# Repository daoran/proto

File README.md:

# proto

`proto` contain notes and code used to learn about different aspects of
robotics. From estimation, mapping to control and planning.

## Build

For convenience there is a `Makefile` that automates the installation of
dependencies and building of `proto`, the make targets are as follows.

```
  deps:
    Install proto dependencies.

  debug:
    Build proto in debug mode.

  release:
    Build proto in release mode.

  install:
    Install proto to $PREFIX. By default this is "/usr/local".

  ros:
    Build the ROS interface to `proto` (a.k.a `proto_ros`).

  format_code:
    Format proto code using clang-format.
```

Or, the standard way to build a C++ project is to enter the following commands
at the root of the repo.

```
  mkdir -p build
  cd build
  cmake ..
  make
  sudo make install  # By default will install to /usr/local
```

## License

The source code is released under MIT license.

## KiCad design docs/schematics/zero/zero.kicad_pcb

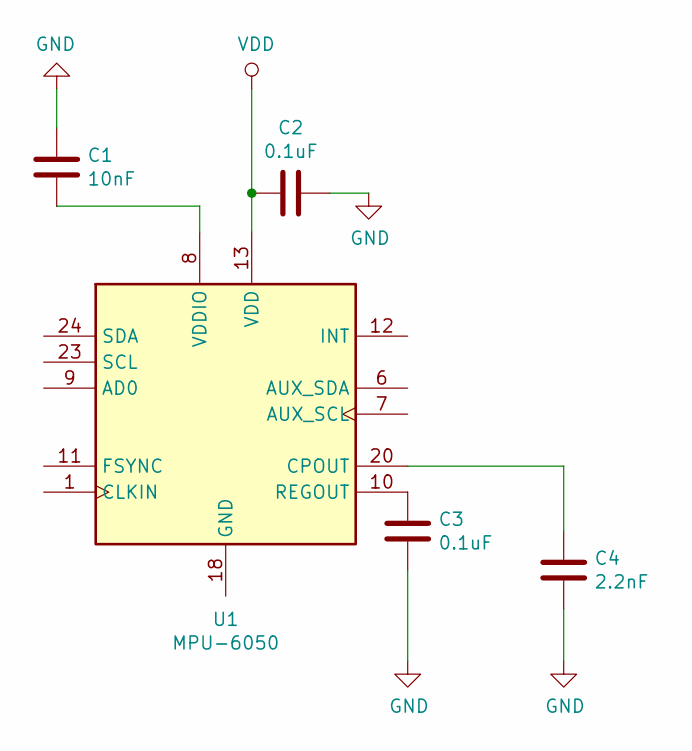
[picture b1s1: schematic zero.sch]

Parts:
C1: 10nF; C_0805_2012Metric
C2, C3: 0.1uF; C_0805_2012Metric
C4: 2.2nF; C_0805_2012Metric
U1: MPU-6050; InvenSense_QFN-24_4x4mm_P0.5mm

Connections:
GND: C1.1, C2.1, C3.2, C4.1
unnamed: C1.2, U1.8 (VDDIO)
unnamed: C3.1, U1.10 (REGOUT)
unnamed: C4.2, U1.20 (CPOUT)
VDD: C2.2, U1.13 (VDD)

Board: 2 copper layers, 5 parts (0 on the bottom side), 5 nets, no tracks yet.

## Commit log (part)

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2024-12-14 Add KDTree to xyz.py
2024-12-14 fix python paths
2024-12-15 Remove scripts/utils
2024-12-15 Remove realsense PwM trigger
2024-12-15 Remove fcu kicad files
2024-12-15 Remove old scripts
2024-12-15 Update exps readme
2024-12-15 Remove old doc
2024-12-15 fix tests and general clean up
2024-12-15 Add gl_entity utility functions
2024-12-15 Rename vector and matrix functions
2024-12-15 Add ability to draw 3D point clouds
2024-12-15 Add points frag and vertex shaders
2024-12-16 Add orbit controls
2024-12-17 Add gl rectangle
2024-12-17 Constrain pitch while rotating camera
2024-12-20 Remove tis and sbgc from xyz.h
2024-12-25 Add KHR and glad
2024-12-25 Modify Makefile for FreeType and GLAD
2024-12-25 Add glad to gitignore
2024-12-26 Add ability to render text
2024-12-26 Add gl_line functions
2024-12-29 Add working gl_image_t
2024-12-31 Update gui
2024-12-31 Move shaders inline
2024-12-31 Remove shaders dir
2024-12-31 Add working button
2025-01-01 Add ability to draw text background
2025-01-04 Complete revamp of notes
2025-01-04 Add fonts
2025-01-04 Fix text not blending background
2025-01-08 Fix text rendering
2025-01-12 Refactor
2025-01-12 Refactor gl_rect functions to use gl_shader_t
2025-01-12 Refactor gl_cube functions to use gl_shader_t
2025-01-12 Refactor draw functions
2025-01-12 Add text_width_height()
2025-01-14 Start working on ui_menu()
2025-01-14 Fix mouse
2025-01-15 Refactor gl_image_t to draw_image()
2025-01-16 Fix button
2025-01-17 Make gui variables global
2025-01-19 Add http.c
2025-01-20 Add gl_vec3_t gl_quat_t gl_pose_t
2025-01-20 Add ambient and spectral lighting to cube
2025-01-23 Add prefix xyz to sources
2025-01-24 Move mav out of src
2025-01-24 Extracting out functions into separate files
2025-01-25 Restructure build
2025-01-26 Restructure
2025-01-26 Fix tests
2025-01-26 Disable euroc test in CI mode
2025-01-26 Fix test
2025-02-03 Add cam_checkerboard to euroc dataset download script
2025-02-03 Add WIP checkerboard_detection.py
2025-02-08 Remove UI elements
2025-02-09 Add print_float_array() print_double_array()
2025-02-09 Add xyz_kitti module
2025-02-09 Add comments
2025-02-16 Add kitti_calib_print()
2025-02-23 Add FLANN as third party
2025-02-23 Add lz4 to third_party
2025-02-23 Update third_party/Makefile
2025-02-23 Add xyz_octree
2025-02-23 Remove pyqtgraph code
2025-02-23 Remove pip_install()
2025-02-23 Remove Gimbal Calibrator
2025-02-23 Fix ts2sec() type hints
2025-02-28 Add umeyama()
2025-02-28 Minor refactor
2025-02-28 Add KittiVelodyneData()
2025-02-28 Make xyz_aprilgrid self sufficient
2025-03-01 Mkae xyz_kitti self sufficient
2025-03-01 Make xyz_control self sufficient
2025-03-02 Add TestPointCloud
2025-03-02 Add .venv to .gitignore
2025-03-03 Add fix_rotation_matrix()
2025-03-03 Update euler321() type hinting
2025-03-03 Remove CameraFactor
2025-03-04 Add rot_diff()
2025-03-04 Add test_icp()
2025-03-08 Remove malloc and calloc macros for gui
2025-03-09 Refactor entities
2025-03-09 Minor updates
2025-03-16 Fix bug in KITTI oxts satellite data
2025-03-16 Refactor gl entities
2025-03-16 Update tests
2025-03-19 Add wait_key()
2025-03-19 Add dotf()
2025-03-19 Add VEC_ADD() and VEC_SUB()
2025-03-19 Add test_idf_factor()
2025-03-19 Remove prints in unittest
2025-03-19 Add point_t
2025-03-26 Add xyz_voxel module
2025-04-05 Refactor out MALLOC() and CALLOC() macros
2025-04-09 Add kdtree_nn()
2025-04-09 Add octree_points()
2025-04-09 Add test_octree_points()
2025-04-10 Add kdtree_data_t
2025-04-12 Add octree_downsample()
2025-04-16 Remove stack and queue from xyz_ds
2025-04-17 Add simpler hashmap implementation that uses linear probing
2025-04-17 Move DSA into xyz
2025-04-17 Fix CI
2025-04-17 Fix CI test
2025-04-24 Add red-black-tree
2025-04-26 Add more unit-tests for rbt
2025-04-26 Update third party dependencies
2025-04-30 Run docker image in github ci
2025-05-01 Switch to using apt for packages
2025-05-01 Update make third_party command
2025-05-03 Remove third_party dir
2025-05-03 Remove Inverse Depth Parameterisation (for now)
2025-05-05 Refactoring marg_factor_t
2025-05-07 Add print_stacktrace()
2025-05-07 Remove xyz_cv
2025-05-07 Remove cv module from config.mk
2025-05-08 Fix test_se
2025-05-09 Rename camera_params_t to camera_t
2025-05-09 Refactor camchain
2025-05-26 Add test_sim_camera_data_load()
2025-05-26 Fix rmdir()
2025-05-28 Refactor test_euroc_imu_load() test_euroc_camera_load()
2025-05-29 Complete refactoring euroc tests
2025-06-05 Refactor kitti tests
2025-06-12 Refactor save_poses() and load_poses()
2025-06-14 Update rbt_contains() take in a const rbt pointer
2025-06-14 Update rbt_contains() API
2025-06-14 Refactor aprilgrid_load()
2025-06-14 Remove position_t
2025-06-14 Remove rotation_t
2025-06-14 Remove pose_t
2025-06-14 Remove extrinsic_t
2025-06-14 Remove fiducial
2025-06-14 Remove velocity
2025-06-14 Remove imu_biases_t
2025-06-14 Remove time_delay_t
2025-06-14 Remove joint_t
2025-06-14 Refactor param_index_add..()
2025-06-14 Refactor param_index_print()
2025-06-14 Refactor unit-tests
2025-06-14 Refactor factors to use raw pointers for params
2025-06-14 Refactor marg_factor_t
2025-06-14 Fix memory leaks
2025-06-19 Add ability to copy key to RBT
2025-06-19 Update rbt tests
2025-06-19 Remove sim_data
2025-06-19 Remove xyz_se.c xyz_se.h
2025-06-19 Clean up test_data
2025-06-19 Fix rbt_delete() again ...
2025-06-20 Update makefile
2025-06-22 Remove Arrow3d
2025-06-28 Refactor FactorGraph into Solver
2025-06-29 Remove TwoStateVisionFactor and GimbalKinematics
2025-07-05 Add CalibTarget
2025-07-05 Remove SimGimbal
2025-07-06 Add stub file for xyz.py
2025-07-06 Use ruff instead of yapf
2025-07-06 Add src/xyz.egg-info to .gitignore
2025-07-13 Add Plane and Frustum
2025-07-16 Add working Plane and Frustum
2025-07-22 Add morton code notes
2025-08-17 Fix gl_points
2025-08-17 Refactor tic() toc()
2025-08-17 Add morton code functions
2025-09-06 Clang-format xyz_http
2025-09-06 Add plot_points.py
2025-09-06 Add torus knot functions
2025-09-06 Add voxel_grid_downsampling()
2025-09-06 cppcheck fix
2025-09-06 Remove test_voxel.c
2025-09-06 Remove docker
2025-09-07 Add gl_line_t
2025-09-08 Trying out typst
2025-09-08 Remove gl_line_t
2025-09-08 Refactor gl_axes3d_t to use gl_line_t
2025-09-14 Refactor munit.h test verbose
2025-09-14 Refactor gl_grid3d_t to use gl_lines3d_t
2025-09-14 Fix gl_image_t
2025-09-20 Umeyama in C
2025-09-20 Rename umeyama to kabsch_umeyama()
2025-09-20 Revert back to calling it umeyama()
2025-10-05 Moving the C code somewhere else - moving to protytping with C++ instead
2025-10-05 Add third_party
2025-10-05 Fix third_party
2025-10-08 Refactor unittest to reflect code structure
2025-10-08 Add Euroc.hpp
2025-10-12 Start creating a cv module
2025-10-12 Start implementing a CalibCameraImuError
2025-10-12 Move static function into source
2025-10-12 Clang format
2025-10-12 Refactor ResidualBlock to automatically convert manifold jacobians to what ceres expects
2025-10-12 Add Kitti and SimVio
2025-10-26 Restructure camera models and distortions
2025-11-16 Fix CalibCameraError
2025-11-19 Add ReprojError
2025-11-22 Fix CalibCameraImuError
2025-11-22 Reverting docs back to Sphinx
2025-11-22 Add requirements.txt
2025-11-22 Add venv and docs/build_ to gitignore
2025-11-24 Add Logger
2025-11-29 Add Kalibr's AprilTag detector
2025-11-29 Fix AprilGrid
2025-11-30 Add camera_id to CalibTarget
2025-11-30 Add parse() for std::filesystem::path
2025-11-30 Add docs make target
2025-12-01 Add multiple target support to CameraChain
2025-12-02 Add CalibTargetChain
2025-12-03 Change license back to MIT
2025-12-03 Add AprilGridConfig
2025-12-03 Add CalibTargetGeometry
2025-12-03 Add TestAprilGridDetector
2025-12-03 Add getters for calibration target geometries in CalibData
2025-12-03 Refactor CalibTargetGeometry
2025-12-04 Add working CalibCamera
2025-12-08 Add working SimCalibCamera
2025-12-08 Fix CalibCamera to check everything is inorder before calibrating
2025-12-10 Fix TestCalibCamera
2025-12-11 Add Kitti dataset loader
2025-12-18 Add Imu::trim() and Imu::extract()
2025-12-18 Refactor Kitti::load_points()
2025-12-18 Refactor CalibCameraImuError to include target extrinsic and target point
2025-12-25 Move Core, Solver and Logger into core module
2025-12-26 Add propagation test for TestLissajousTrajectory
2025-12-30 Refactor ImuError
2025-12-31 Fix ImuError
2025-12-31 Disable Logger tests
2025-12-31 Add loger to TestImuError
2025-12-31 Remove mav module
2025-12-31 Rename third_party to deps
2025-12-31 Fix unused compilation warning
2025-12-31 Fix Makefile
2025-12-31 Change namespace from xyz to cartesian
2025-12-31 Remove docs
2025-12-31 Clean up scripts
2025-12-31 Remove python files
2026-01-11 Add Euroc and Kitti unit-tests
2026-01-24 Remove custom filesystem functions -> using std::filesystem instead
2026-03-29 Refactor logger colors to be Vec3i
2026-03-29 Add SimCircle
2026-03-29 Fix Euroc
2026-05-17 Add CalibProblem::setupSolver()
2026-05-17 Remove exps
2026-05-17 Add SO3 hand-eye optimization
2026-05-17 Add CalibInit::initializeCameraIntrinsics() and CalibInit::initializeCameraExtrinsics()
2026-05-23 Add CalibInit::initialize_intrinsics test
2026-05-23 Add CalibInit.hpp to calib.hpp
2026-05-23 Add TODO
2026-05-23 Refactor CalibTarget methods to use snake case
2026-05-23 Refactor AprilGrid methods to use snake case
2026-05-23 Add make format-code
2026-05-23 Fix build
2026-05-23 Add apriltags-imgs to deps
2026-05-23 Automatically download git submodule if the git repo has submodules
2026-05-23 Make method names snake cases
2026-05-23 Add unittest make target
2026-05-24 Refactor CalibTargetGeometry::setExtrinsic to CalibTargetGeoemtry::set_extrinsic
2026-05-24 Fix make_aprilgrid
2026-05-24 Add docstrings to make_aprilgrid.py
2026-05-24 Add .style.yapf
2026-05-24 Add multiple calibration target detection support
2026-05-25 Make AprilGridConfig, CameraGeometry use snake cases
2026-05-25 Refactor lib/ceres to use snake cases for method names
2026-05-25 Add relwithdeb make target
2026-05-25 Add time delay parameter to CalibProblem
2026-05-25 Refactor I() to eye() and add CalibCameraImuError2.cpp
2026-05-25 Add docs
2026-05-25 Remove CalibCameraImuError2
2026-05-30 Fix compilation warnings
2026-05-30 Add Plane
2026-05-31 Remove zombie code
2026-05-31 Rename CameraData to CalibTargetData
2026-05-31 Refactor CalibTarget to be a struct
2026-05-31 Add CalibCameraImuError2
2026-06-06 Add time delay to CalibProblem
2026-06-06 Update CalibCameraImuError2
2026-06-06 Add SO3::exp()
2026-06-07 Add SO3::right_jacobian() and SO3::right_jacobian_inv()
2026-06-07 Update sim module
2026-06-07 Add both pixel velocity and pose interpolation methods for estimating camera-imu time delay in CalibCameraImuError
2026-06-07 Update ResidualBlock
2026-06-07 Update CalibCameraImuError
2026-06-13 Add clean target to Makefile
2026-06-13 Fix jacobiSvd template syntax for Eigen 3.4
2026-06-13 Move td_method mode assignment outside loop in add_view
2026-06-13 Move time delay from camera to IMU in SimCalib simulation
2026-06-13 Update download_dataset.py to also download calibration sequences
2026-06-13 Fix Kitti
2026-06-13 Add Colormap
2026-06-13 Add pcl to deps
2026-06-13 Add pcl to gitignore
